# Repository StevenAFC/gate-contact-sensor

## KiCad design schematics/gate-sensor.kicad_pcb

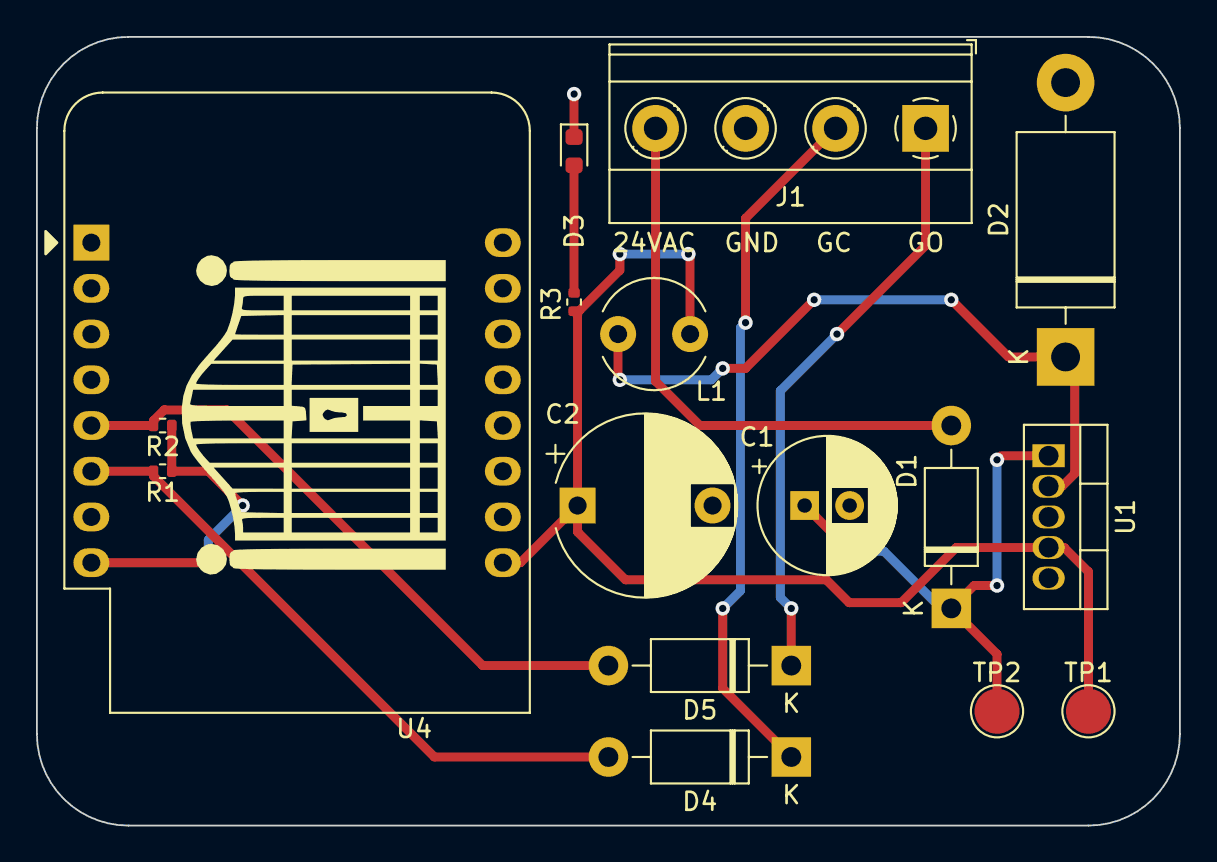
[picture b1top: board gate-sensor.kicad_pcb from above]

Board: 2 copper layers, 63.5 x 43.8 mm, 16 parts (0 on the bottom side), 11 nets.

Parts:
C1: 220uF; CP_Radial_D7.5mm_P2.50mm
C2: 1000uf; CP_Radial_D10.0mm_P7.50mm
D1, D4, D5: 1N4007; D_DO-41_SOD81_P10.16mm_Horizontal
D2: 1N5822; D_DO-201AD_P15.24mm_Horizontal
D3: LED; LED_0603_1608Metric
J1: Screw_Terminal_01x04; TerminalBlock_Phoenix_MKDS-1,5-4_1x04_P5.00mm_Horizontal
L1: 100uH; L_Radial_D6.0mm_P4.00mm
R1, R2: 1k; R_0402_1005Metric
R3: 120 ohm; R_0402_1005Metric
TP1, TP2: TestPoint; TestPoint_Pad_D2.5mm
U1: LM2576T-5; TO-220-5_Vertical
U4: WeMos_D1_mini; WEMOS_D1_mini_light

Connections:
3.3v: R1.1, R2.1, U4.8 (3V3)
5v: C2.1, L1.2, R3.1, TP1.1, U1.4 (FB), U4.9 (5V)
24v: C1.1, D1.1 (K), TP2.1, U1.1 (VIN)
AC: D1.2 (A), J1.4
GC 3.3v: D4.2 (A), R1.2, U4.6 (MOSI/D7)
GC 5v: D4.1 (K), J1.2
GND: C1.2, C2.2, D2.2 (A), D3.1 (K), J1.3, U1.3 (GND), U1.5 (~ON/OFF), U4.10 (GND)
GO 3.3v: D5.2 (A), R2.2, U4.5 (MISO/D6)
GO 5v: D5.1 (K), J1.1
unnamed: D2.1 (K), L1.1, U1.2 (OUT)
unnamed: D3.2 (A), R3.2

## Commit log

2022-02-23 Send status on 5 second loop
2022-02-23 Uploading schematics
2022-02-25 rename KiCad project
2022-02-25 Ignore KiCad cache file
2022-02-25 Remove cache file
